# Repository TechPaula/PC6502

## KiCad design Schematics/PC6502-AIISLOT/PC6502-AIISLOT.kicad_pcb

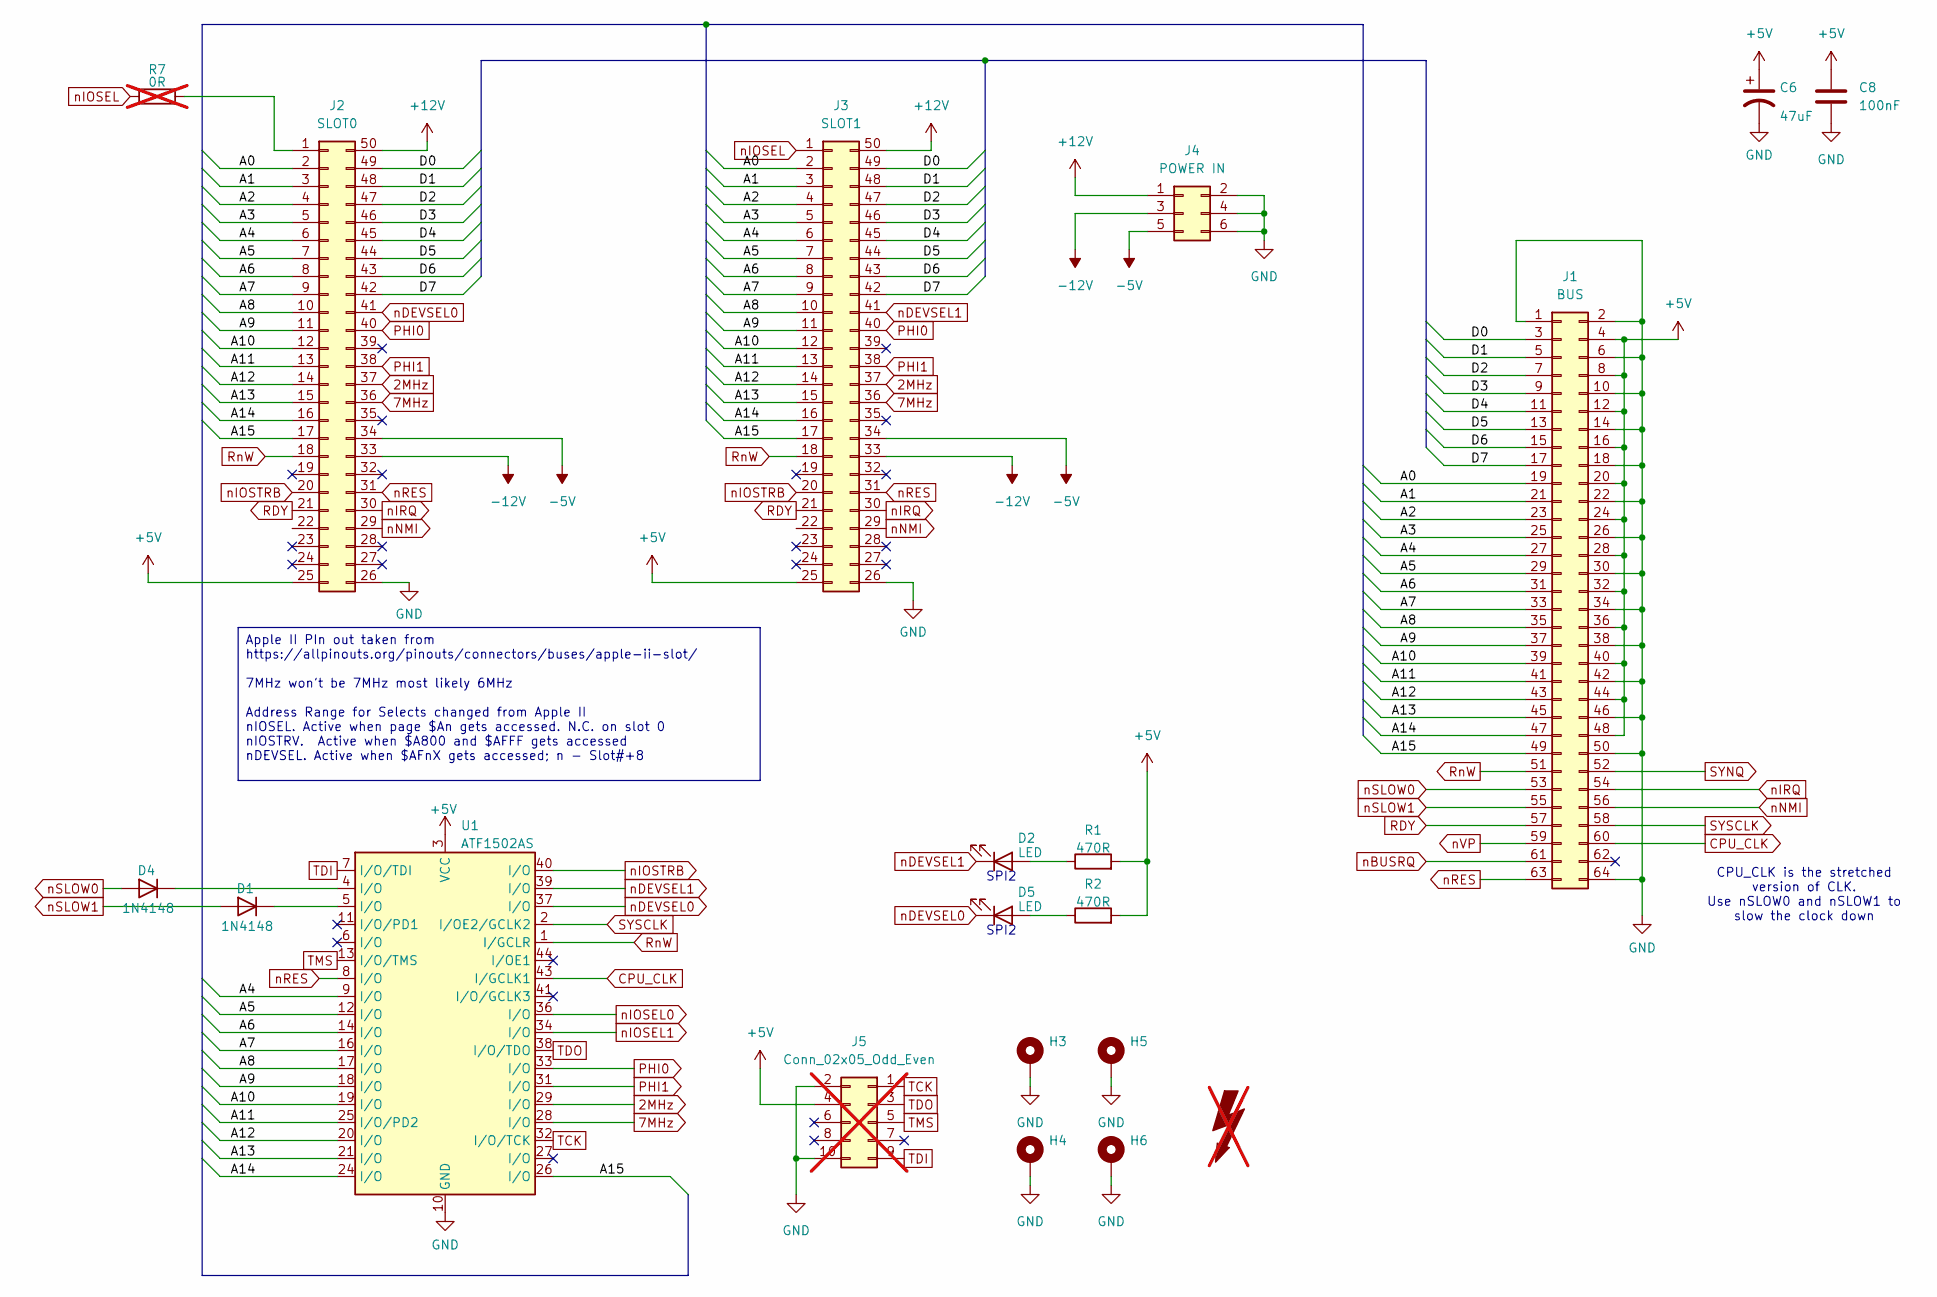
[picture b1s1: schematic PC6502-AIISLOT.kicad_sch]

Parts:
C6: 47uF; C_1206_3216Metric; LCSC C96123
C8: 100nF; C_0805_2012Metric
D1, D4: 1N4148; D_DO-35_SOD27_P7.62mm_Horizontal; LCSC DNF
D2, D5: LED; LTL4221NHBP
FOX1: SYM_Flash_Large; Fox_avatar_18mm; LCSC DNF; not fitted
H3, H4, H5, H6: MountingHole_Pad; MountingHole_3.2mm_M3_Pad_TopBottom; LCSC DNF
J1: BUS; PinSocket_2x32_P2.54mm_Vertical; LCSC DNF
J2: SLOT0; 55308435_APPLEII
J3: SLOT1; 55308435_APPLEII
J4: POWER IN; PinHeader_2x03_P2.54mm_Horizontal
J5: Conn_02x05_Odd_Even; PinHeader_2x05_P2.54mm_Vertical; LCSC DNF; not fitted
R1, R2: 470R; R_0603_1608Metric_Pad0.98x0.95mm_HandSolder
R7: 0R; R_0603_1608Metric_Pad0.98x0.95mm_HandSolder; not fitted
U1: ATF1502AS; PLCC-44_THT-Socket; LCSC DNF

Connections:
2MHz: J2.37, J3.37, U1.29 (I/O)
7MHz: J2.36, J3.36, U1.28 (I/O)
+5V: C6.1, C8.1, J1.4, J1.8, J1.12, J1.16, J1.20, J1.24, J1.28, J1.32, J1.36, J1.40, J1.44, J1.48, J2.25, J3.25, J5.4, R1.2, R2.2, U1.3 (VCC), U1.15 (VCC), U1.23 (VCC), U1.35 (VCC)
+12V: J2.50, J3.50, J4.1
-5V: J2.34, J3.34, J4.5
-12V: J2.33, J3.33, J4.3
/A0: J1.19, J2.2, J3.2
/A1: J1.21, J2.3, J3.3
/A2: J1.23, J2.4, J3.4
/A3: J1.25, J2.5, J3.5
/A4: J1.27, J2.6, J3.6, U1.9 (I/O)
/A5: J1.29, J2.7, J3.7, U1.12 (I/O)
/A6: J1.31, J2.8, J3.8, U1.14 (I/O)
/A7: J1.33, J2.9, J3.9, U1.16 (I/O)
/A8: J1.35, J2.10, J3.10, U1.17 (I/O)
/A9: J1.37, J2.11, J3.11, U1.18 (I/O)
/A10: J1.39, J2.12, J3.12, U1.19 (I/O)
/A11: J1.41, J2.13, J3.13, U1.25 (I/O/PD2)
/A12: J1.43, J2.14, J3.14, U1.20 (I/O)
/A13: J1.45, J2.15, J3.15, U1.21 (I/O)
/A14: J1.47, J2.16, J3.16, U1.24 (I/O)
/A15: J1.49, J2.17, J3.17, U1.26 (I/O)
/D0: J1.3, J2.49, J3.49
/D1: J1.5, J2.48, J3.48
/D2: J1.7, J2.47, J3.47
/D3: J1.9, J2.46, J3.46
/D4: J1.11, J2.45, J3.45
/D5: J1.13, J2.44, J3.44
/D6: J1.15, J2.43, J3.43
/D7: J1.17, J2.42, J3.42
CPU_CLK: J1.60, U1.43 (I/GCLK1)
GND: C6.2, C8.2, H3.1, H4.1, H5.1, H6.1, J1.1, J1.2, J1.6, J1.10, J1.14, J1.18, J1.22, J1.26, J1.30, J1.34, J1.38, J1.42, J1.46, J1.50, J1.64, J2.26, J3.26, J4.2, J4.4, J4.6, J5.2, J5.10, U1.10 (GND), U1.22 (GND), U1.30 (GND), U1.42 (GND)
unnamed: D1.1 (K), U1.5 (I/O)
unnamed: D2.2 (A), R1.1
unnamed: D4.1 (K), U1.4 (I/O)
unnamed: D5.2 (A), R2.1
unnamed: J2.1, R7.2
PHI0: J2.40, J3.40, U1.33 (I/O)
PHI1: J2.38, J3.38, U1.31 (I/O)
RDY: J1.57, J2.21, J3.21
RnW: J1.51, J2.18, J3.18, U1.1 (I/GCLR)
SYNQ: J1.52
SYSCLK: J1.58, U1.2 (I/OE2/GCLK2)
TCK: J5.1, U1.32 (I/O/TCK)
TDI: J5.9, U1.7 (I/O/TDI)
TDO: J5.3, U1.38 (I/O/TDO)
TMS: J5.5, U1.13 (I/O/TMS)
nBUSRQ: J1.61
nDEVSEL0: D5.1 (K), J2.41, U1.37 (I/O)
nDEVSEL1: D2.1 (K), J3.41, U1.39 (I/O)
nIOSEL: J3.1, R7.1
nIOSEL0: U1.36 (I/O)
nIOSEL1: U1.34 (I/O)
nIOSTRB: J2.20, J3.20, U1.40 (I/O)
nIRQ: J1.54, J2.30, J3.30
nNMI: J1.56, J2.29, J3.29
nRES: J1.63, J2.31, J3.31, U1.8 (I/O)
nSLOW0: D4.2 (A), J1.53
nSLOW1: D1.2 (A), J1.55
nVP: J1.59

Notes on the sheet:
CPU_CLK is the stretched version of CLK. Use nSLOW0 and nSLOW1 to slow the clock down
SPI2
Apple II PIn out taken from https://allpinouts.org/pinouts/connectors/buses/apple-ii-slot/ 7MHz won't be 7MHz most likely 6MHz Address Range for Selects changed from Apple II nIOSEL. Active when page $An gets accessed. N.C. on slot 0 nIOSTRV. Active when $A800 and $AFFF gets accessed nDEVSEL. Activ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

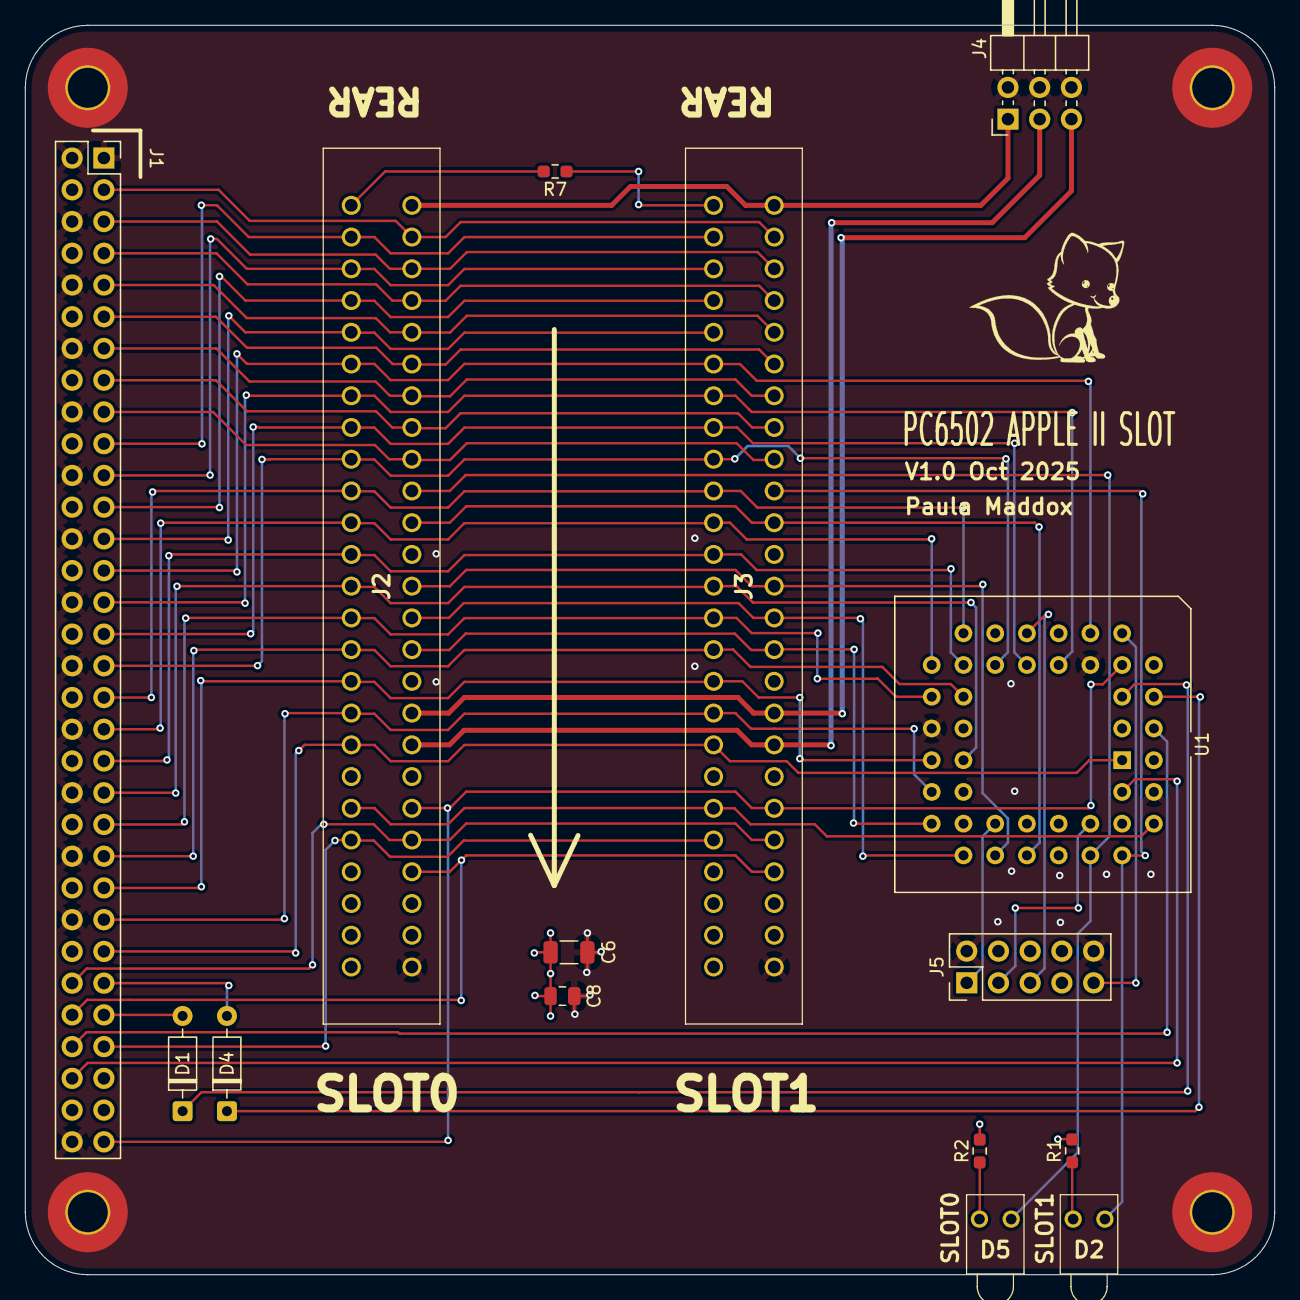
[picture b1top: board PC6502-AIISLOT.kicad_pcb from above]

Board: 4 copper layers, 100.0 x 100.0 mm, 20 parts (0 on the bottom side), 55 nets.

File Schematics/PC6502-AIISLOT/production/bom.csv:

Designator,Footprint,Quantity,Value,LCSC Part #
C6,1206,1,47uF,C96123
C8,0805,1,100nF,
"D1, D4",D_DO-35_SOD27_P7.62mm_Horizontal,2,1N4148,DNF
"D2, D5",LTL4221NHBP,2,LED,
"H3, H4, H5, H6",MountingHole_3.2mm_M3_Pad_TopBottom,4,MountingHole_Pad,DNF
J1,PinSocket_2x32_P2.54mm_Vertical,1,BUS,DNF
J2,55308435_APPLEII,1,SLOT0,
J3,55308435_APPLEII,1,SLOT1,
J4,PinHeader_2x03_P2.54mm_Horizontal,1,POWER IN,
J5,PinHeader_2x05_P2.54mm_Vertical,1,Conn_02x05_Odd_Even,DNF
"R1, R2",0603,2,470R,
R7,0603,1,0R,
U1,PLCC-44_THT-Socket,1,ATF1502AS,DNF

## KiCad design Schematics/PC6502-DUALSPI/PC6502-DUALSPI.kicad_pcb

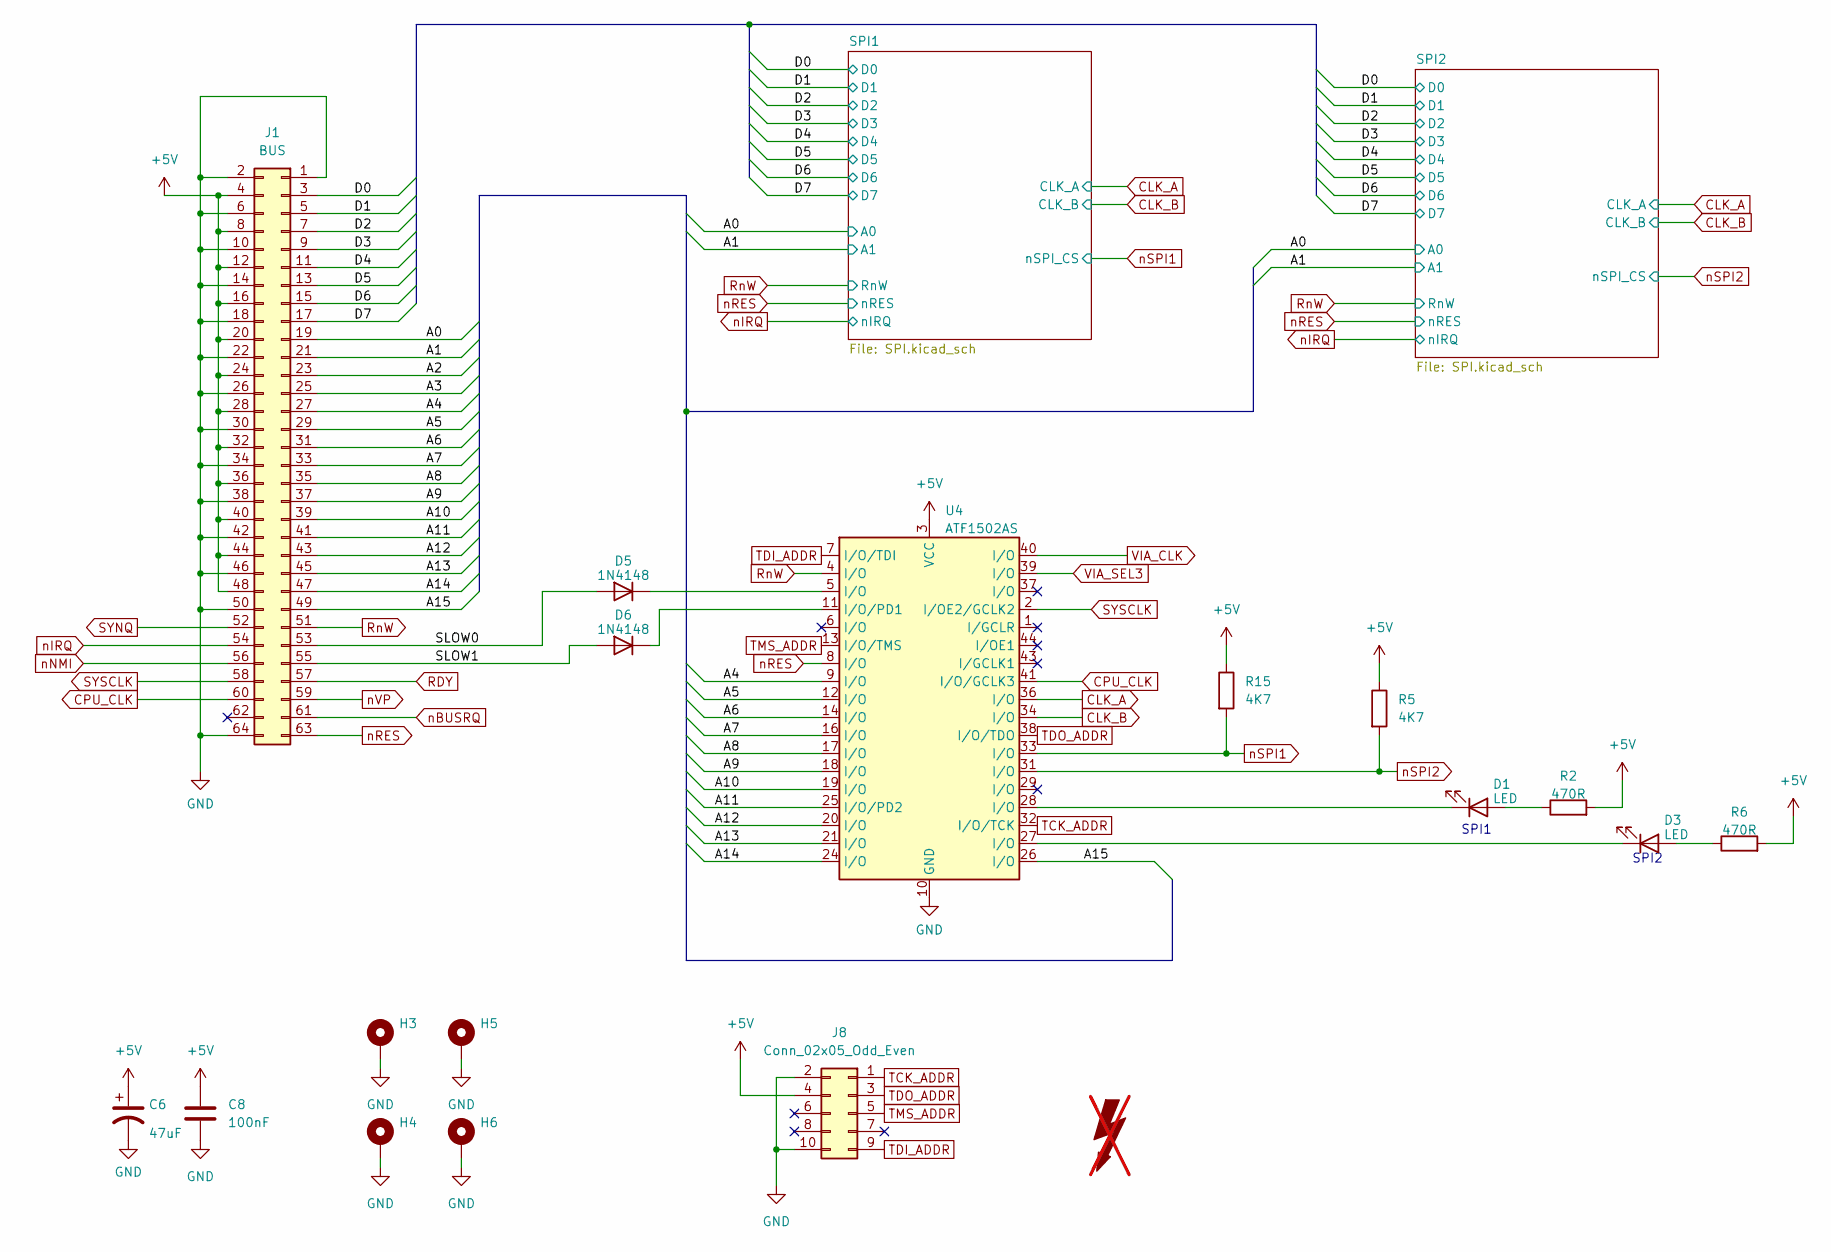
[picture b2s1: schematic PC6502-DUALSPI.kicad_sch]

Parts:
C6: 47uF; C_1206_3216Metric; LCSC C96123
C8: 100nF; C_0805_2012Metric
D1, D3: LED; LTL4221NHBP
D5, D6: 1N4148; D_DO-35_SOD27_P7.62mm_Horizontal; LCSC DNF
FOX1: SYM_Flash_Large; Fox_avatar_18mm; LCSC DNF; not fitted
H3, H4, H5, H6: MountingHole_Pad; MountingHole_3.2mm_M3_Pad_TopBottom; LCSC DNF
J1: BUS; PinSocket_2x32_P2.54mm_Vertical; LCSC DNF
J8: Conn_02x05_Odd_Even; PinHeader_2x05_P2.54mm_Vertical
R2, R6: 470R; R_0603_1608Metric_Pad0.98x0.95mm_HandSolder
R5, R15: 4K7; R_0603_1608Metric_Pad0.98x0.95mm_HandSolder
U4: ATF1502AS; PLCC-44_THT-Socket

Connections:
+5V: C6.1, C8.1, J1.4, J1.8, J1.12, J1.16, J1.20, J1.24, J1.28, J1.32, J1.36, J1.40, J1.44, J1.48, J8.4, R2.2, R5.1, R6.2, R15.1, U4.3 (VCC), U4.15 (VCC), U4.23 (VCC), U4.35 (VCC); also elsewhere on the board
/A0: J1.19; also elsewhere on the board
/A1: J1.21; also elsewhere on the board
/A2: J1.23
/A3: J1.25
/A4: J1.27, U4.9 (I/O)
/A5: J1.29, U4.12 (I/O)
/A6: J1.31, U4.14 (I/O)
/A7: J1.33, U4.16 (I/O)
/A8: J1.35, U4.17 (I/O)
/A9: J1.37, U4.18 (I/O)
/A10: J1.39, U4.19 (I/O)
/A11: J1.41, U4.25 (I/O/PD2)
/A12: J1.43, U4.20 (I/O)
/A13: J1.45, U4.21 (I/O)
/A14: J1.47, U4.24 (I/O)
/A15: J1.49, U4.26 (I/O)
/D0: J1.3; also elsewhere on the board
/D1: J1.5; also elsewhere on the board
/D2: J1.7; also elsewhere on the board
/D3: J1.9; also elsewhere on the board
/D4: J1.11; also elsewhere on the board
/D5: J1.13; also elsewhere on the board
/D6: J1.15; also elsewhere on the board
/D7: J1.17; also elsewhere on the board
/SLOW0: D5.2 (A), J1.53
/SLOW1: D6.2 (A), J1.55
CLK_A: U4.36 (I/O); also elsewhere on the board
CLK_B: U4.34 (I/O); also elsewhere on the board
CPU_CLK: J1.60, U4.41 (I/O/GCLK3); also elsewhere on the board
GND: C6.2, C8.2, H3.1, H4.1, H5.1, H6.1, J1.1, J1.2, J1.6, J1.10, J1.14, J1.18, J1.22, J1.26, J1.30, J1.34, J1.38, J1.42, J1.46, J1.50, J1.64, J8.2, J8.10, U4.10 (GND), U4.22 (GND), U4.30 (GND), U4.42 (GND); also elsewhere on the board
unnamed: D1.2 (A), R2.1
unnamed: D1.1 (K), U4.28 (I/O)
unnamed: D3.2 (A), R6.1
unnamed: D3.1 (K), U4.27 (I/O)
unnamed: D5.1 (K), U4.5 (I/O)
unnamed: D6.1 (K), U4.11 (I/O/PD1)
RDY: J1.57
RnW: J1.51, U4.4 (I/O); also elsewhere on the board
SYNQ: J1.52
SYSCLK: J1.58, U4.2 (I/OE2/GCLK2); also elsewhere on the board
TCK_ADDR: J8.1, U4.32 (I/O/TCK)
TDI_ADDR: J8.9, U4.7 (I/O/TDI)
TDO_ADDR: J8.3, U4.38 (I/O/TDO)
TMS_ADDR: J8.5, U4.13 (I/O/TMS)
VIA_CLK: U4.40 (I/O)
VIA_SEL3: U4.39 (I/O)
nBUSRQ: J1.61
nIRQ: J1.54; also elsewhere on the board
nNMI: J1.56
nRES: J1.63, U4.8 (I/O); also elsewhere on the board
nSPI1: R15.2, U4.33 (I/O); also elsewhere on the board
nSPI2: R5.2, U4.31 (I/O); also elsewhere on the board
nVP: J1.59

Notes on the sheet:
SPI1
SPI2

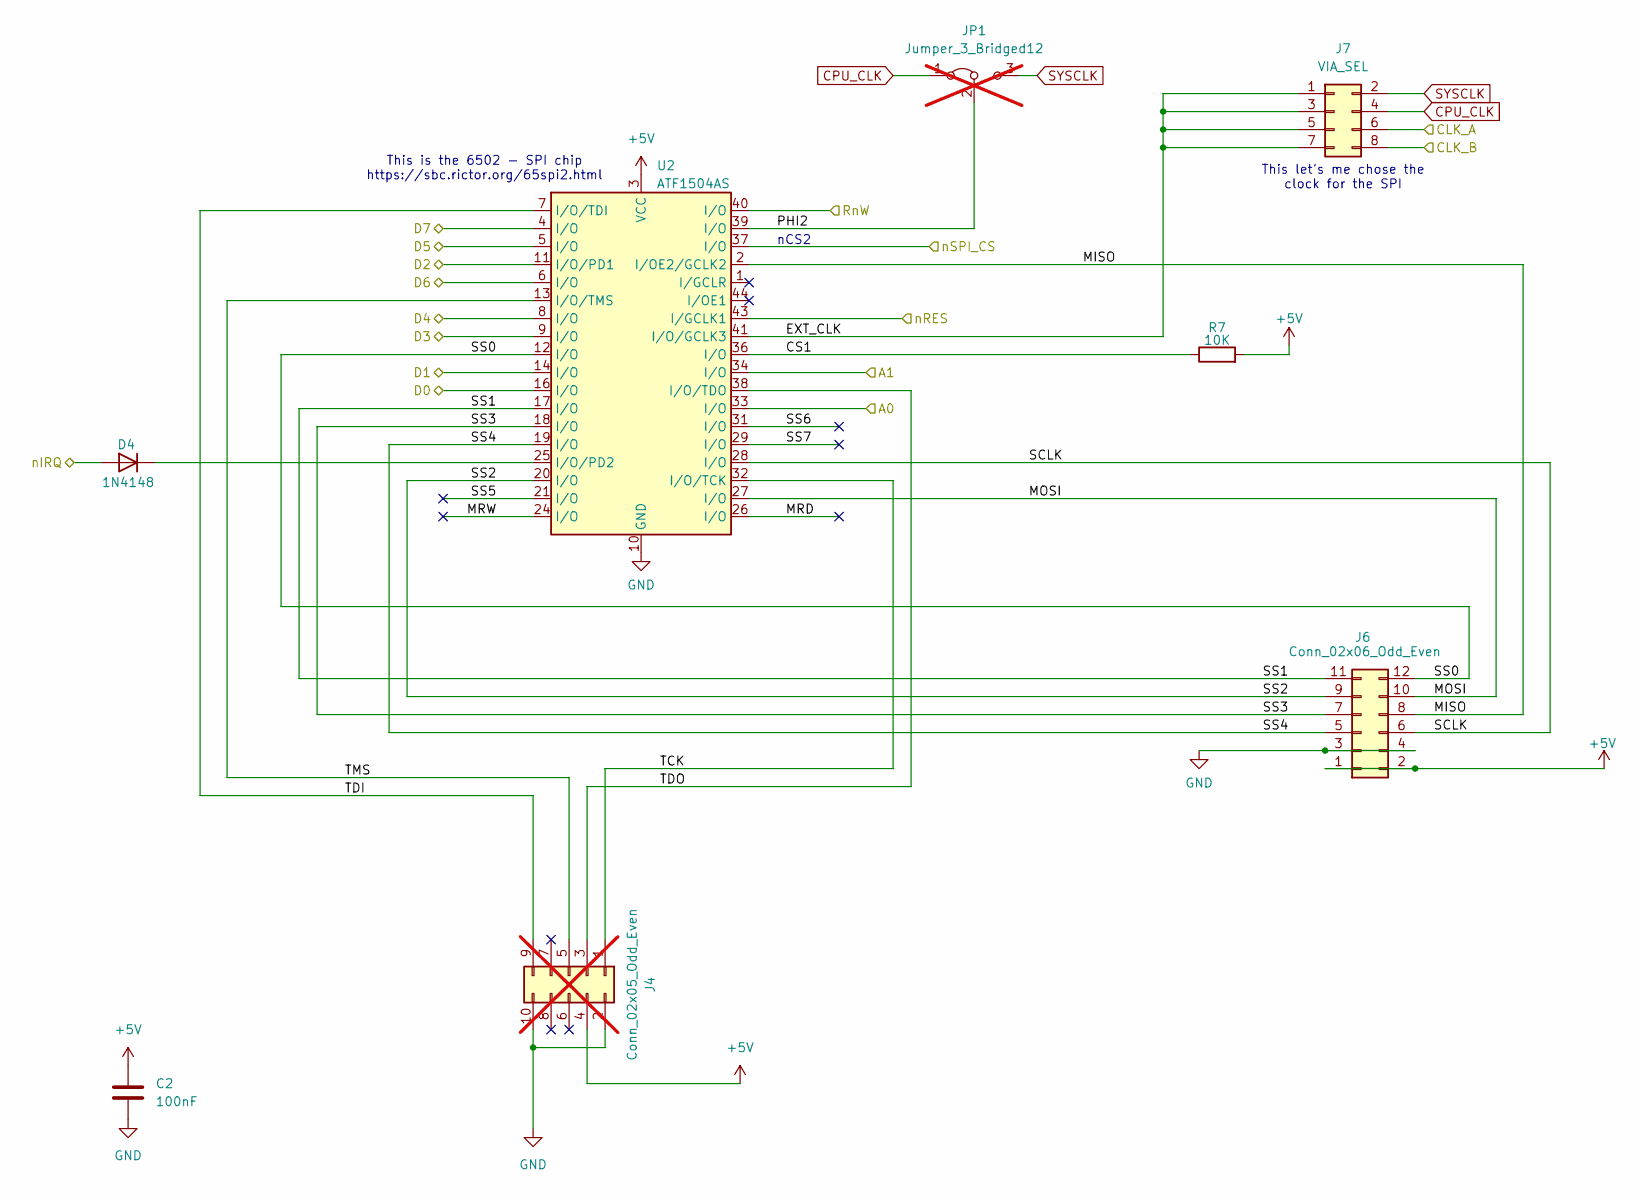
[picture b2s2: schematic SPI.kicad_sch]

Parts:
C2: 100nF; C_0805_2012Metric
D4: 1N4148; D_DO-35_SOD27_P7.62mm_Horizontal; LCSC DNF
J4: Conn_02x05_Odd_Even; PinHeader_2x05_P2.54mm_Vertical; LCSC DNF; not fitted
J6: Conn_02x06_Odd_Even; PinSocket_2x06_P2.54mm_Horizontal
J7: VIA_SEL; PinHeader_2x04_P2.54mm_Horizontal
JP1: Jumper_3_Bridged12; SolderJumper-3_P1.3mm_Bridged12_RoundedPad1.0x1.5mm_NumberL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; LCSC DNF; not fitted
R7: 10K; R_0603_1608Metric_Pad0.98x0.95mm_HandSolder
U2: ATF1504AS; PLCC-44_THT-Socket; LCSC DNP

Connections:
+5V: C2.1, J4.4, J6.1, J6.2, R7.2, U2.3 (VCC), U2.15 (VCC), U2.23 (VCC), U2.35 (VCC); also elsewhere on the board
/A0: U2.33 (I/O); also elsewhere on the board
/A1: U2.34 (I/O); also elsewhere on the board
/D0: U2.16 (I/O); also elsewhere on the board
/D1: U2.14 (I/O); also elsewhere on the board
/D2: U2.11 (I/O/PD1); also elsewhere on the board
/D3: U2.9 (I/O); also elsewhere on the board
/D4: U2.8 (I/O); also elsewhere on the board
/D5: U2.5 (I/O); also elsewhere on the board
/D6: U2.6 (I/O); also elsewhere on the board
/D7: U2.4 (I/O); also elsewhere on the board
/SPI1/CS1: R7.1, U2.36 (I/O)
/SPI1/EXT_CLK: J7.1, J7.3, J7.5, J7.7, U2.41 (I/O/GCLK3)
/SPI1/MISO: J6.8, U2.2 (I/OE2/GCLK2)
/SPI1/MOSI: J6.10, U2.27 (I/O)
/SPI1/MRD: U2.26 (I/O)
/SPI1/MRW: U2.24 (I/O)
/SPI1/PHI2: JP1.2 (C), U2.39 (I/O)
/SPI1/SCLK: J6.6, U2.28 (I/O)
/SPI1/SS0: J6.12, U2.12 (I/O)
/SPI1/SS1: J6.11, U2.17 (I/O)
/SPI1/SS2: J6.9, U2.20 (I/O)
/SPI1/SS3: J6.7, U2.18 (I/O)
/SPI1/SS4: J6.5, U2.19 (I/O)
/SPI1/SS5: U2.21 (I/O)
/SPI1/SS6: U2.31 (I/O)
/SPI1/SS7: U2.29 (I/O)
/SPI1/TCK: J4.1, U2.32 (I/O/TCK)
/SPI1/TDI: J4.9, U2.7 (I/O/TDI)
/SPI1/TDO: J4.3, U2.38 (I/O/TDO)
/SPI1/TMS: J4.5, U2.13 (I/O/TMS)
CLK_A: J7.6; also elsewhere on the board
CLK_B: J7.8; also elsewhere on the board
CPU_CLK: J7.4, JP1.1 (A); also elsewhere on the board
GND: C2.2, J4.2, J4.10, J6.3, J6.4, U2.10 (GND), U2.22 (GND), U2.30 (GND), U2.42 (GND); also elsewhere on the board
unnamed: D4.1 (K), U2.25 (I/O/PD2)
RnW: U2.40 (I/O); also elsewhere on the board
SYSCLK: J7.2, JP1.3 (B); also elsewhere on the board
nIRQ: D4.2 (A); also elsewhere on the board
nRES: U2.43 (I/GCLK1); also elsewhere on the board
nSPI1: U2.37 (I/O); also elsewhere on the board

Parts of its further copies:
C1: 100nF; C_0805_2012Metric
D2: 1N4148; D_DO-35_SOD27_P7.62mm_Horizontal; LCSC DNF
J2: Conn_02x05_Odd_Even; PinHeader_2x05_P2.54mm_Vertical; LCSC DNF; not fitted
J3: Conn_02x06_Odd_Even; PinSocket_2x06_P2.54mm_Horizontal
J5: VIA_SEL; PinHeader_2x04_P2.54mm_Horizontal
JP2: Jumper_3_Bridged12; SolderJumper-3_P1.3mm_Bridged12_RoundedPad1.0x1.5mm_NumberL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; LCSC DNF; not fitted
R4: 10K; R_0603_1608Metric_Pad0.98x0.95mm_HandSolder
U1: ATF1504AS; PLCC-44_THT-Socket; LCSC DNP

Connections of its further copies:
+5V: C1.1, J2.4, J3.1, J3.2, R4.2, U1.3 (VCC), U1.15 (VCC), U1.23 (VCC), U1.35 (VCC); also elsewhere on the board
/A0: U1.33 (I/O); also elsewhere on the board
/A1: U1.34 (I/O); also elsewhere on the board
/D0: U1.16 (I/O); also elsewhere on the board
/D1: U1.14 (I/O); also elsewhere on the board
/D2: U1.11 (I/O/PD1); also elsewhere on the board
/D3: U1.9 (I/O); also elsewhere on the board
/D4: U1.8 (I/O); also elsewhere on the board
/D5: U1.5 (I/O); also elsewhere on the board
/D6: U1.6 (I/O); also elsewhere on the board
/D7: U1.4 (I/O); also elsewhere on the board
/SPI2/CS1: R4.1, U1.36 (I/O)
/SPI2/EXT_CLK: J5.1, J5.3, J5.5, J5.7, U1.41 (I/O/GCLK3)
/SPI2/MISO: J3.8, U1.2 (I/OE2/GCLK2)
/SPI2/MOSI: J3.10, U1.27 (I/O)
/SPI2/MRD: U1.26 (I/O)
/SPI2/MRW: U1.24 (I/O)
/SPI2/PHI2: JP2.2 (C), U1.39 (I/O)
/SPI2/SCLK: J3.6, U1.28 (I/O)
/SPI2/SS0: J3.12, U1.12 (I/O)
/SPI2/SS1: J3.11, U1.17 (I/O)
/SPI2/SS2: J3.9, U1.20 (I/O)
/SPI2/SS3: J3.7, U1.18 (I/O)
/SPI2/SS4: J3.5, U1.19 (I/O)
/SPI2/SS5: U1.21 (I/O)
/SPI2/SS6: U1.31 (I/O)
/SPI2/SS7: U1.29 (I/O)
/SPI2/TCK: J2.1, U1.32 (I/O/TCK)
/SPI2/TDI: J2.9, U1.7 (I/O/TDI)
/SPI2/TDO: J2.3, U1.38 (I/O/TDO)
/SPI2/TMS: J2.5, U1.13 (I/O/TMS)
CLK_A: J5.6; also elsewhere on the board
CLK_B: J5.8; also elsewhere on the board
CPU_CLK: J5.4, JP2.1 (A); also elsewhere on the board
GND: C1.2, J2.2, J2.10, J3.3, J3.4, U1.10 (GND), U1.22 (GND), U1.30 (GND), U1.42 (GND); also elsewhere on the board
unnamed: D2.1 (K), U1.25 (I/O/PD2)
RnW: U1.40 (I/O); also elsewhere on the board
SYSCLK: J5.2, JP2.3 (B); also elsewhere on the board
nIRQ: D2.2 (A); also elsewhere on the board
nRES: U1.43 (I/GCLK1); also elsewhere on the board
nSPI2: U1.37 (I/O); also elsewhere on the board

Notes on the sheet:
This let's me chose the clock for the SPI
This is the 6502 - SPI chip https://sbc.rictor.org/65spi2.html
nCS2

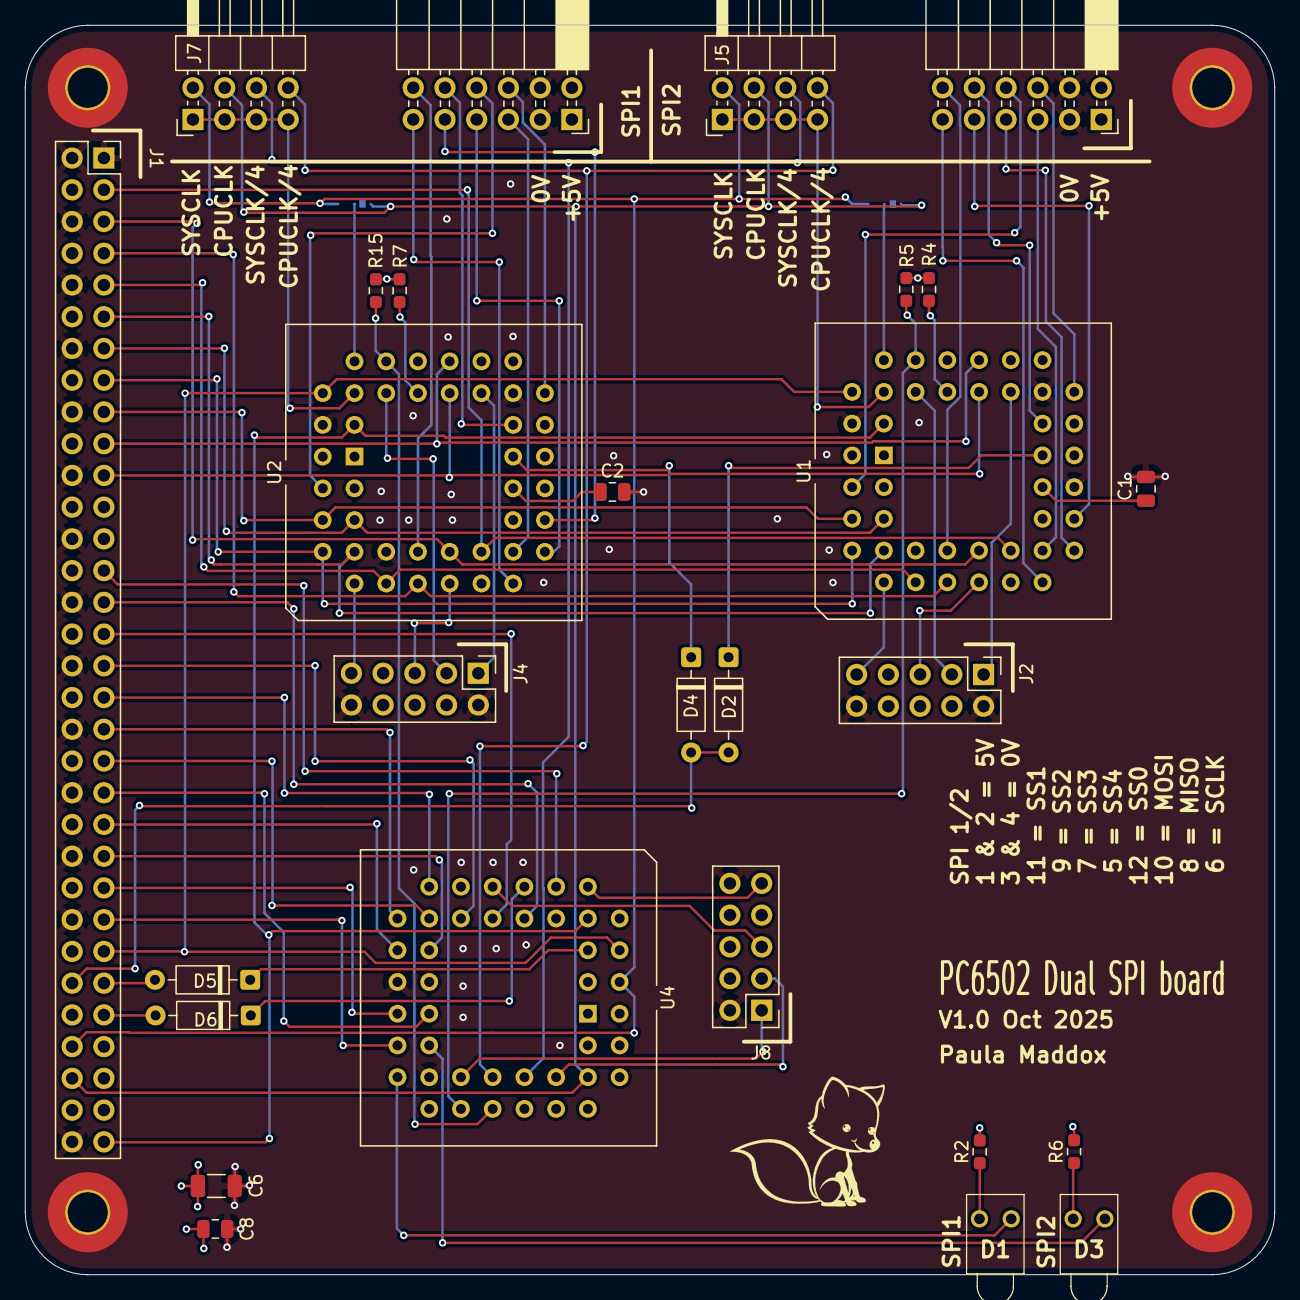
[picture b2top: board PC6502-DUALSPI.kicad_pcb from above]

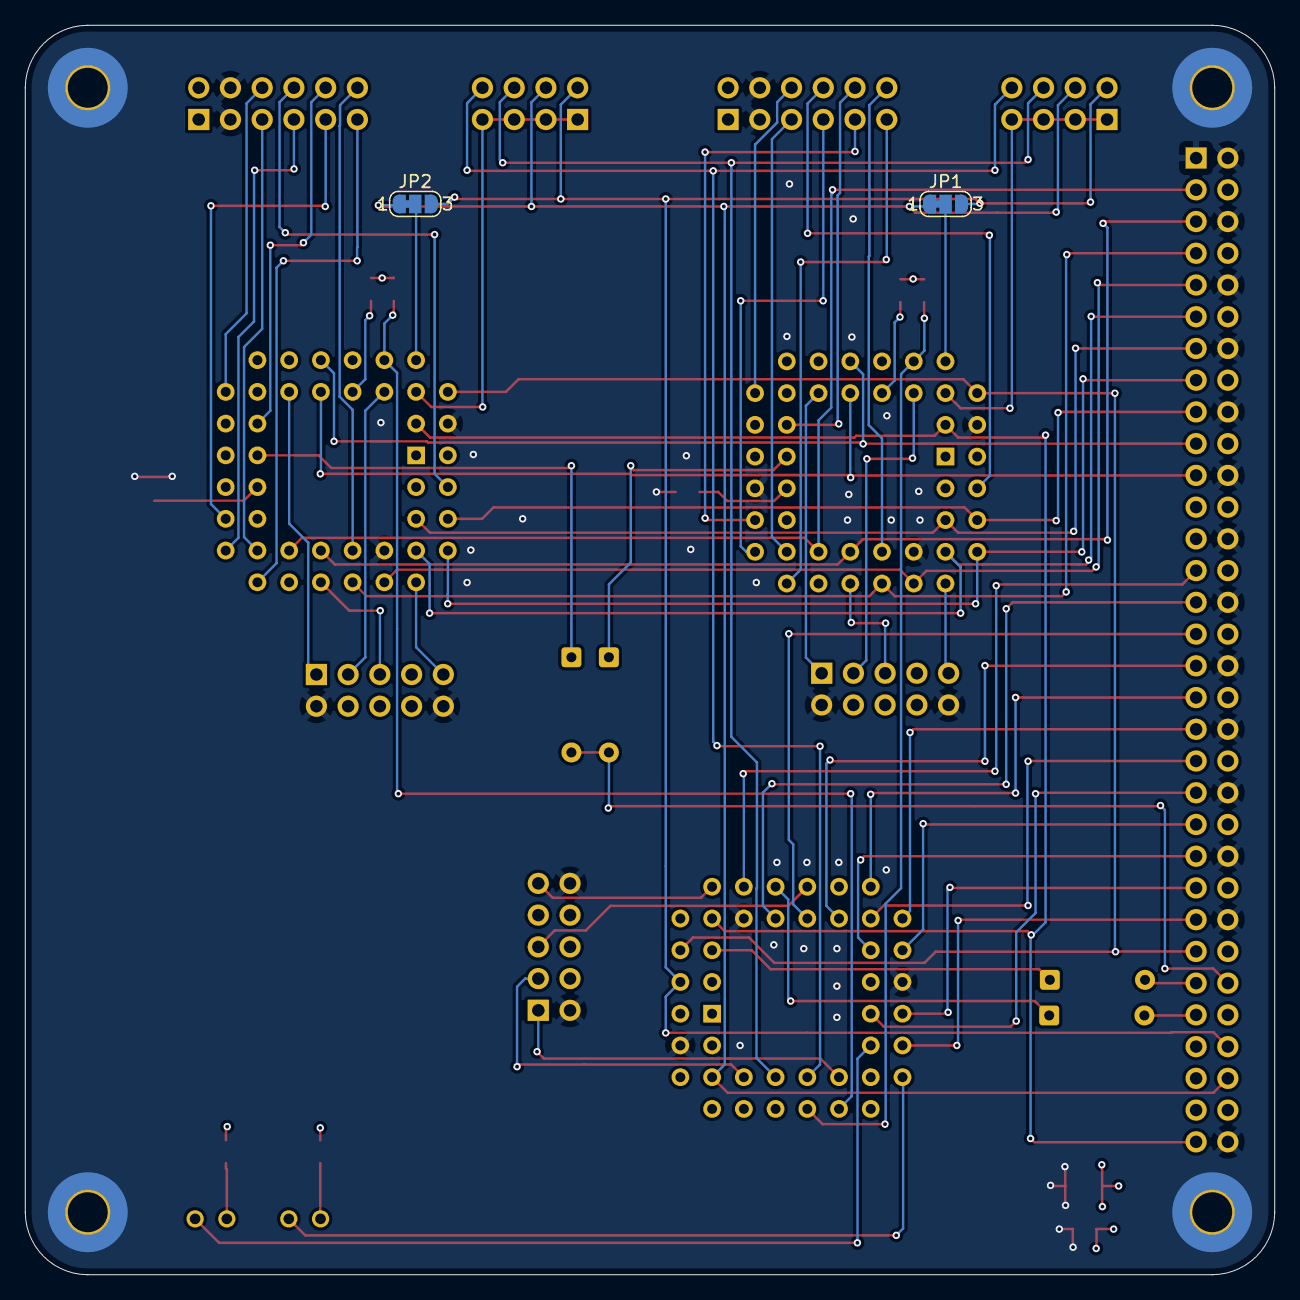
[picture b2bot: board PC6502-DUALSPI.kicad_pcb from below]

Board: 4 copper layers, 100.0 x 100.0 mm, 34 parts (2 on the bottom side), 77 nets.

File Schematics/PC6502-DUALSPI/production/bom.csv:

Designator,Footprint,Quantity,Value,LCSC Part #
"C1, C2, C8",0805,3,100nF,
C6,1206,1,47uF,C96123
"D1, D3",LTL4221NHBP,2,LED,
"D2, D4, D5, D6",D_DO-35_SOD27_P7.62mm_Horizontal,4,1N4148,DNF
"H3, H4, H5, H6",MountingHole_3.2mm_M3_Pad_TopBottom,4,MountingHole_Pad,DNF
J1,PinSocket_2x32_P2.54mm_Vertical,1,BUS,DNF
"J2, J4",PinHeader_2x05_P2.54mm_Vertical,2,Conn_02x05_Odd_Even,DNF
"J3, J6",PinSocket_2x06_P2.54mm_Horizontal,2,Conn_02x06_Odd_Even,
"J5, J7",PinHeader_2x04_P2.54mm_Horizontal,2,VIA_SEL,
J8,PinHeader_2x05_P2.54mm_Vertical,1,Conn_02x05_Odd_Even,
"R15, R5",0603,2,4K7,
"R2, R6",0603,2,470R,
"R4, R7",0603,2,10K,
"U1, U2",PLCC-44_THT-Socket,2,ATF1504AS,DNP
U4,PLCC-44_THT-Socket,1,ATF1502AS,
